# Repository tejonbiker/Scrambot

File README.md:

Scrambot
========

29/May/2014

University of Guanajuato

Division de Ingenierias Campus Irapuato Salamanca (DICIS)

Jose Federico Ramos Ortega

Scrambot is a differential mobile robot controlled via WiFi based
on a beetle robot from Steren as chassis and a Raspberry Pi as core of the controller.

This project begins with the ASME SPDC contest in 2013: "Remote Inspection Device":

https://www.asme.org/events/competitions/student-design-competition

The targets and the rules were quite simple:

    -The robot operator cannot see the stage
    -The robot need to establish (in any way) a real time video with the operator
    -The robot need to be controlled wirelessly
    -The robot need to accomplish three tasks:
      1.-Read a label with four numbers
      2.-Carry a small wood cylinder
      3.-Push a button 
          
The best balance between cost and flexibility was the Raspberry Pi with a lot of add-ons.
The result of the contest was this project (with a more little post work), this repo have the intention
to be a source of knowledge and contact that you require if you want to reconstruct/improve this project. 

Some topics/knowledge used in this robot are:

    -Remote connections
      -SSH
      -VNC
      -TCP sockets for server and client (ANSIC C and Java respectively)
      -MJPEG Server
      
    -Java Desktop GUI
      -Sockets
      -MJPEG Capture and show
      
    -PCB Design (with Eagle)
      -5V Switched Mode Power Suypply
      -Raspberry Pi GPIO and two L293 H-Bridge interface
      
    -Raspberry Pi GPIO management
      -WiringPi
      -I2C (for MPU6050 acelerometter)
      
    -Power Management 
      -Knowledge about batteries (NiCd - Lipo)
      -5V SMPS design
      -Power consumption analysis
      
    -Linux stuff
      -SSH and console commands management
      -Bash scripting
        -Automatically start services
        -Automatically install software
      -Make for compilation in ANSI C
      
    -Wireless LAN magagement
      -Detecting the Scrambot in LAN
      -Scrambot as hotspot
  
(Breathe.......) and much more.

For any misspelling/correction/comment/idea don't doubt to contact me.

tejonbiker@gmail.com

We will be happy if you like the project. 

Don't forget this is a MIT licensed project.

Have fun!!!!! :D

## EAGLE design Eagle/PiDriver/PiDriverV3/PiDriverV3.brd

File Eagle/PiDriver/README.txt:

PiDrive
This board designed to interface four motors with complete H-bridge, 
this task is accomplished with two L293 IC, some other sutff is addded,
like a PIC (MCU) to monitor the input voltage for the motors, the PIC is
not tested yet.

The board don't integrate a regulador to feed the Raspberry Pi with the
battery of the motors, this board only connect the battery for the motors.

The MPU6050 pinout works perfect.

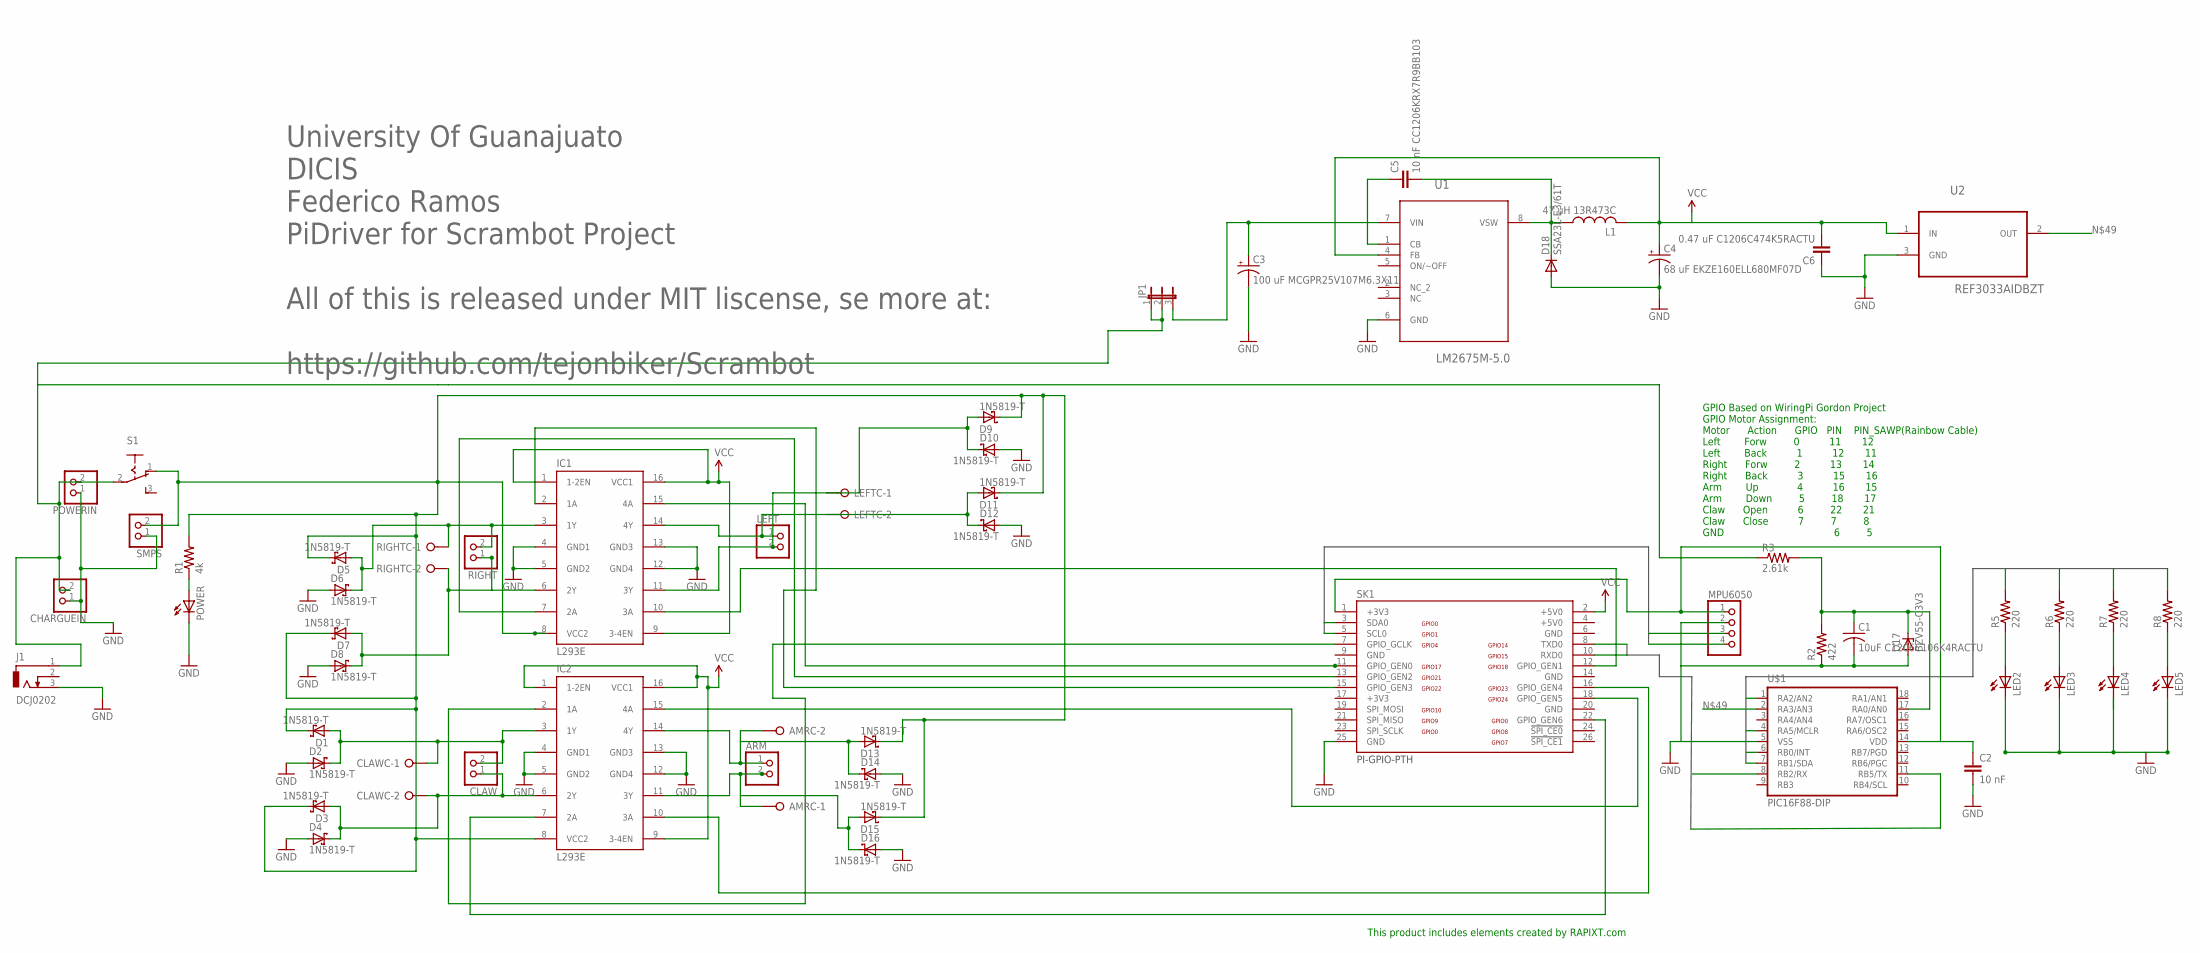
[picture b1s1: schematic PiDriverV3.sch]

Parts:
AMRC: W237-02P; W237-132
ARM: PINHD-1X2; 1X02
C1: 10uF C1206C106K4RACTU; C1206
C2: 10 nF; C1206
C3: 100 uF MCGPR25V107M6.3X11; E1,8-4
C4: 68 uF EKZE160ELL680MF07D; E1,8-4
C5: 10 nF CC1206KRX7R9BB103; C1206
C6: 0.47 uF C1206C474K5RACTU; C1206
CHARGUEIN: PINHD-1X2; 1X02
CLAW: PINHD-1X2; 1X02
CLAWC: W237-02P; W237-132
D1, D2, D3, D4, D5, D6, D7, D8, D9, D10, D11, D12, D13, D14, D15, D16: 1N5819-T; DO41-7.6
D17: BZV55-C3V3; SOD80C
D18: SSA23L-E3/61T; DO-214AC
IC1, IC2: L293E; DIL16
J1: DCJ0202
JP1: JP2E; JP2
L1: 47 uH 13R473C; 6000-XXXX-RC
LED2, LED3, LED4, LED5: LEDSMT1206; 1206
LEFT: PINHD-1X2; 1X02
LEFTC: W237-02P; W237-132
MPU6050: PINHD-1X4; 1X04
POWER: LEDSMT1206; 1206
POWERIN: PINHD-1X2; 1X02
R1: 4k; M1206
R2: 422; M1206
R3: 2.61k; M1206
R5, R6, R7, R8: 220; M1206
RIGHT: PINHD-1X2; 1X02
RIGHTC: W237-02P; W237-132
S1: 255SB
SK1: PI-GPIO-PTH; GPIO-CONNECTOR
SMPS: PINHD-1X2; 1X02
U1: LM2675M-5.0; SOIC127P620X175-8N
U2: REF3033AIDBZT; SOT95P237X112-3N
U$1: PIC16F88-DIP; DIL18

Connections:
+3V3: SK1.17 (+3V3)
+5V0: SK1.4 (+5V0)
ARMC: IC2.2 (1A), SK1.7 (GPIO_GCLK)
GND: C6.1, U2.3 (GND)
HTX: SK1.8 (TXD0), U$1.8 (RB2/RX)
unnamed: POWER.A, R1.1
unnamed: LED2.A, R5.1
unnamed: D9.A, D10.C, IC1.11 (3Y), LEFT.2, LEFTC.1
unnamed: IC2.10 (3A), SK1.16 (GPIO_GEN4)
unnamed: IC1.2 (1A), SK1.15 (GPIO_GEN3)
unnamed: IC1.7 (2A), SK1.13 (GPIO_GEN2)
unnamed: IC1.10 (3A), SK1.12 (GPIO_GEN1)
unnamed: D1.C, D3.C, D5.C, D7.C, D9.C, D11.C, D13.C, D15.C, IC1.8 (VCC2), IC2.8 (VCC2), R1.2, S1.1 (O), SMPS.2
unnamed: AMRC.2, ARM.1, D13.A, D14.C, IC2.14 (4Y)
unnamed: AMRC.1, ARM.2, D15.A, D16.C, IC2.11 (3Y)
unnamed: D11.A, D12.C, IC1.14 (4Y), LEFT.1, LEFTC.2
unnamed: R5.2, U$1.1 (RA2/AN2)
unnamed: C2.1, MPU6050.1, SK1.1 (+3V3), U$1.14 (VDD)
unnamed: IC2.15 (4A), SK1.18 (GPIO_GEN5)
unnamed: LED3.A, R6.1
unnamed: IC2.7 (2A), SK1.22 (GPIO_GEN6)
unnamed: SK1.10 (RXD0), U$1.11 (RB5/TX)
unnamed: CLAW.2, CLAWC.1, D1.A, D2.C, IC2.3 (1Y)
unnamed: D5.A, D6.C, IC1.3 (1Y), RIGHT.2, RIGHTC.1
unnamed: C5.2, D18.C, L1.1, U1.8 (VSW)
unnamed: IC1.15 (4A), SK1.11 (GPIO_GEN0)
unnamed: C3.+, JP1.3, U1.7 (VIN)
unnamed: C1.1, D17.C, R2.2, R3.2, U$1.17 (RA0/AN0)
unnamed: R6.2, U$1.4 (RA5/MCLR)
unnamed: LED4.A, R7.1
unnamed: CLAW.1, CLAWC.2, D3.A, D4.C, IC2.6 (2Y)
unnamed: D7.A, D8.C, IC1.6 (2Y), RIGHT.1, RIGHTC.2
unnamed: LED5.A, R8.1
unnamed: C5.1, U1.1 (CB)
unnamed: R7.2, U$1.6 (RB0/INT)
unnamed: C1.2, C2.2, C3.-, C4.-, CHARGUEIN.1, D2.A, D4.A, D6.A, D8.A, D10.A, D12.A, D14.A, D16.A, D17.A, D18.A, IC1.4 (GND1), IC1.5 (GND2), IC1.12 (GND4), IC1.13 (GND3), IC2.4 (GND1), IC2.5 (GND2), IC2.12 (GND4), IC2.13 (GND3), J1.3, LED2.C, LED3.C, LED4.C, LED5.C, MPU6050.2, POWER.C, POWERIN.1, R2.1, SK1.6 (GND), SK1.9 (GND), SK1.14 (GND), SK1.20 (GND), SK1.25 (GND), SMPS.1, U1.6 (GND), U$1.5 (VSS)
unnamed: R8.2, U$1.7 (RB1/SDA)
unnamed: U2.2 (OUT), U$1.2 (RA3/AN3)
unnamed: CHARGUEIN.2, J1.1, JP1.1, JP1.2, POWERIN.2, R3.1, S1.2
SCL: MPU6050.3, SK1.5 (SCL0)
SDA: MPU6050.4, SK1.3 (SDA0)
VCC: C4.+, C6.2, IC1.1 (1-2EN), IC1.9 (3-4EN), IC1.16 (VCC1), IC2.1 (1-2EN), IC2.9 (3-4EN), IC2.16 (VCC1), L1.2, SK1.2 (+5V0), U1.4 (FB), U2.1 (IN)

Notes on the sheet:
GPIO Based on WiringPi Gordon Project GPIO Motor Assignment: Motor Action GPIO PIN PIN_SAWP(Rainbow Cable) Left Forw 0 11 12 Left Back 1 12 11 Right Forw 2 13 14 Right Back 3 15 16 Arm Up 4 16 15 Arm Down 5 18 17 Claw Open 6 22 21 Claw Close 7 7 8 GND 6 5
This product includes elements created by RAPIXT.com
University Of Guanajuato DICIS Federico Ramos PiDriver for Scrambot Project All of this is released under MIT liscense, se more at: https://github.com/tejonbiker/Scrambot

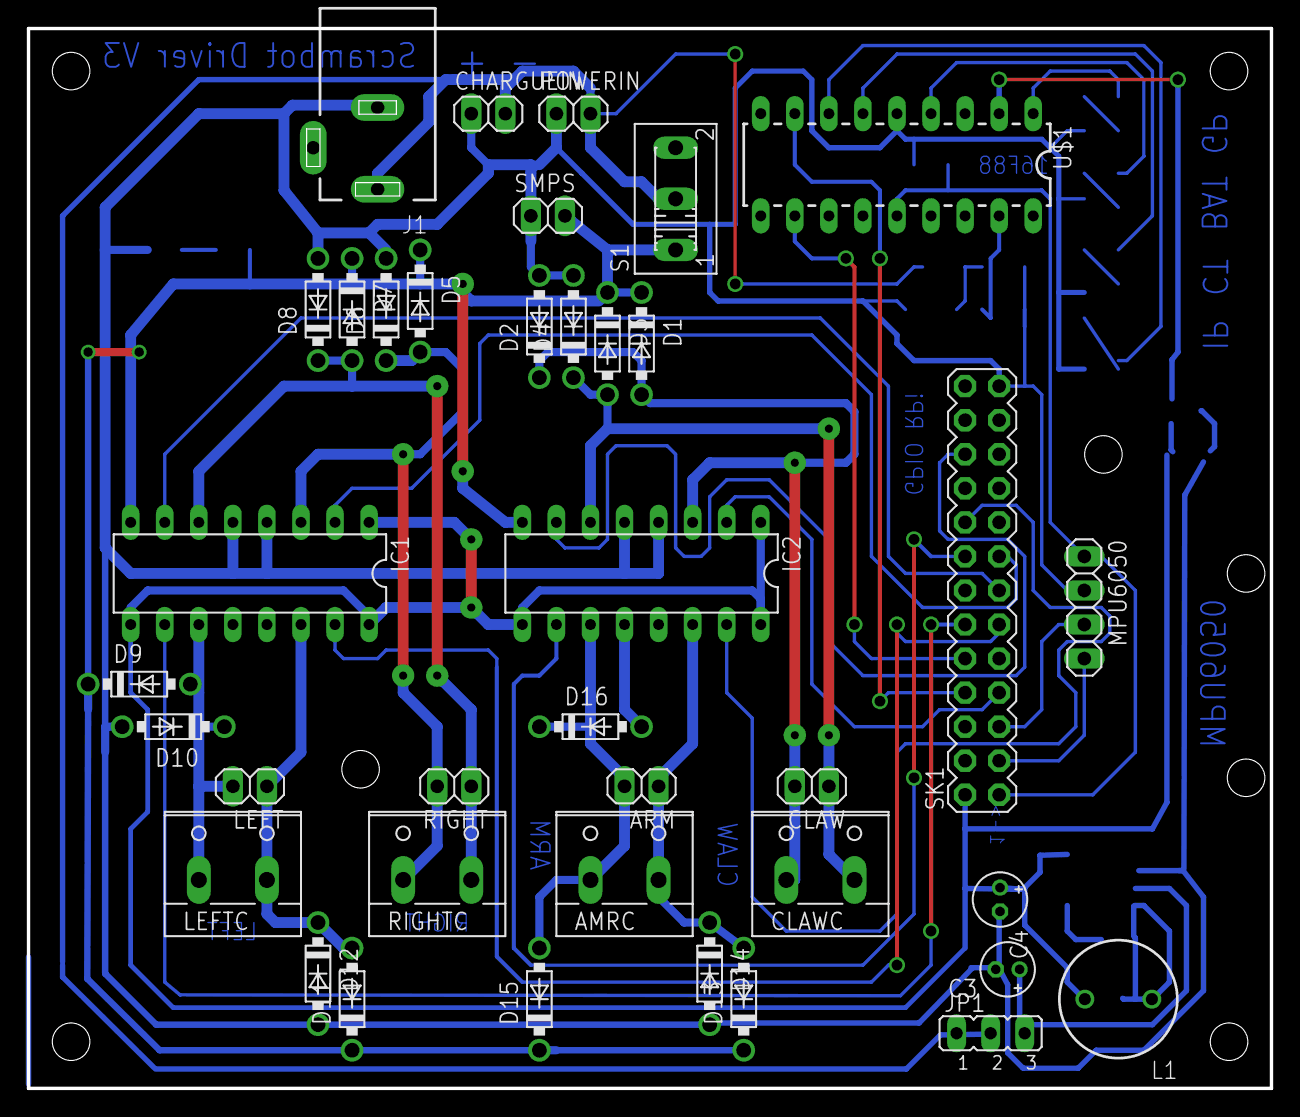
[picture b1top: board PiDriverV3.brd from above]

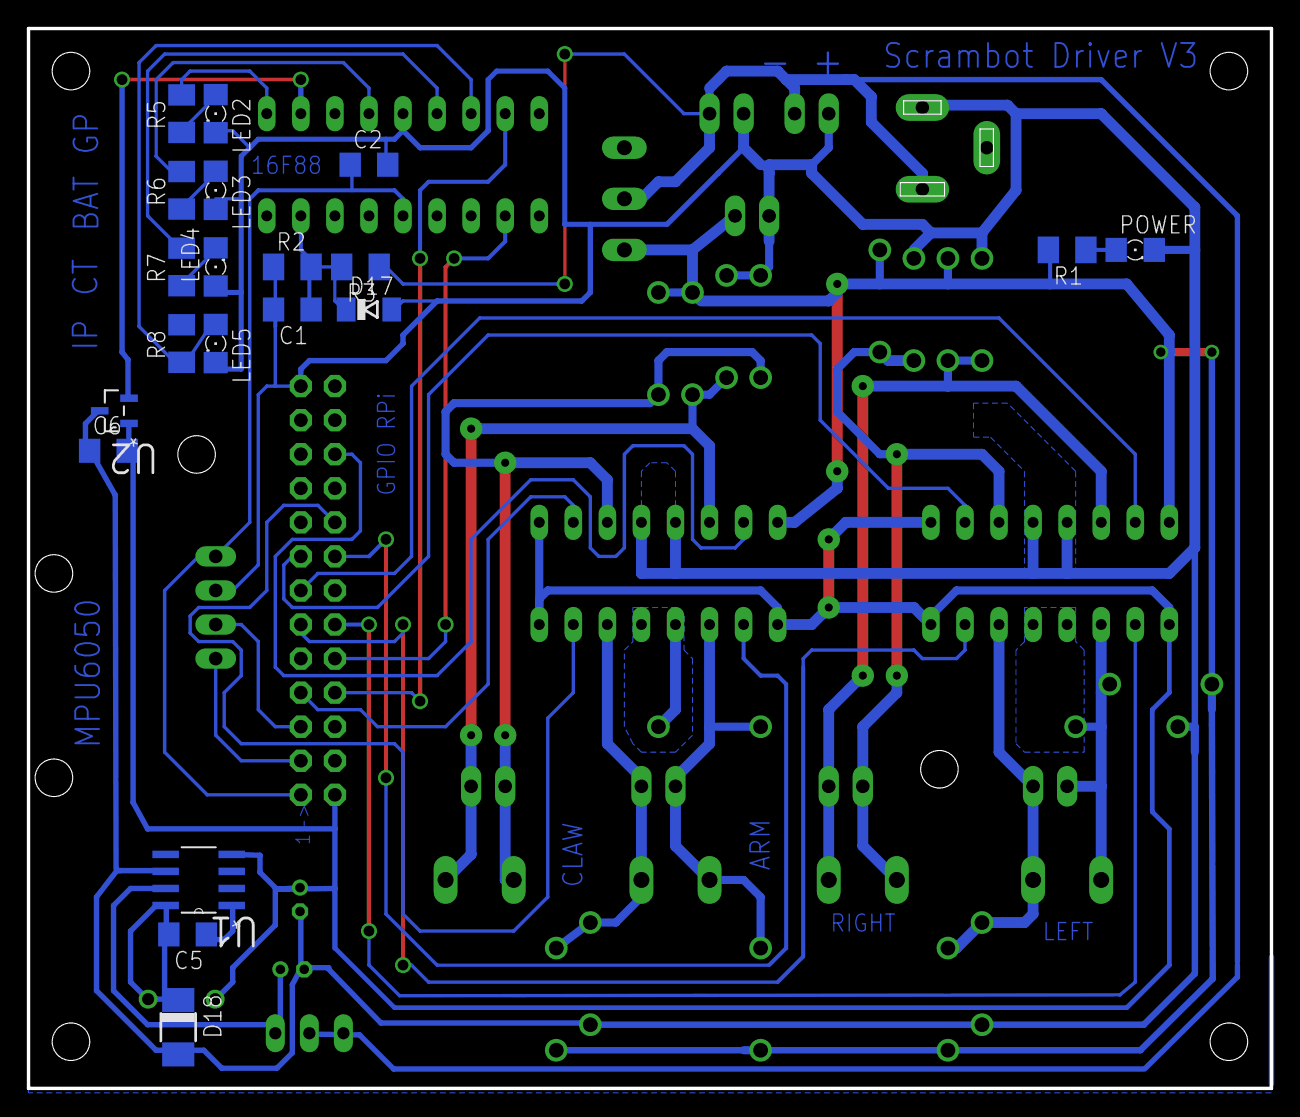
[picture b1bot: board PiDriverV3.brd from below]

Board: 2 copper layers, 92.7 x 79.0 mm, 58 parts (20 on the bottom side), 40 nets.

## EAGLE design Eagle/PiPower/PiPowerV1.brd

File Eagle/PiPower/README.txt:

PiPower
This board is designed to regulate 5V from 7V-15V battery
 voltage with an efficient  Switched Mode Power Supply, 
the board integrate an USB Female A conector to use a 
micro usb cable to power the pi, as is usual.

See more at datasheet of: LM2596

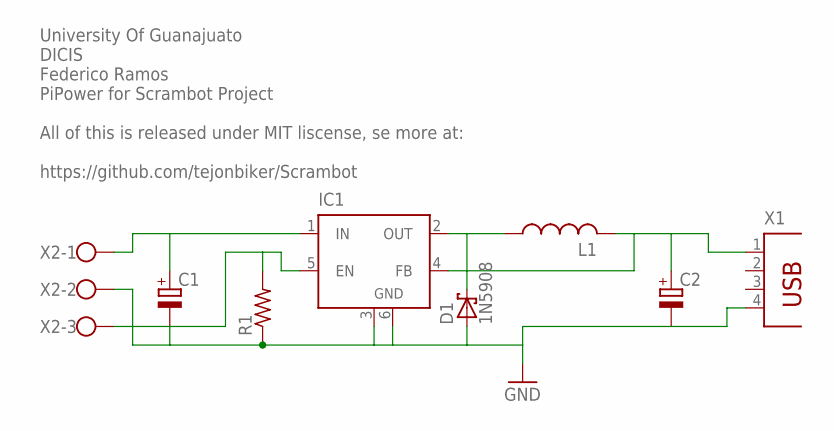
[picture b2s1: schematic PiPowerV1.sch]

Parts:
C1, C2: CPOL-EUE3.5-10; E3,5-10
D1: 1N5908; C4111-15
IC1: LM2596S; TO263-5
L1: L-US0204/5; 0204/5
R1: R-US_M1206; M1206
X1: PN87520
X2: W237-103

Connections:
unnamed: C2.+, IC1.4 (FB), L1.2, X1.1
unnamed: C1.+, IC1.1 (IN), X2.1
unnamed: IC1.5 (EN), R1.2, X2.3
unnamed: D1.C, IC1.2 (OUT), L1.1
unnamed: C1.-, C2.-, D1.A, IC1.3 (GND), IC1.6 (GND), R1.1, X1.4, X2.2

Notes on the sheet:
University Of Guanajuato DICIS Federico Ramos PiPower for Scrambot Project All of this is released under MIT liscense, se more at: https://github.com/tejonbiker/Scrambot

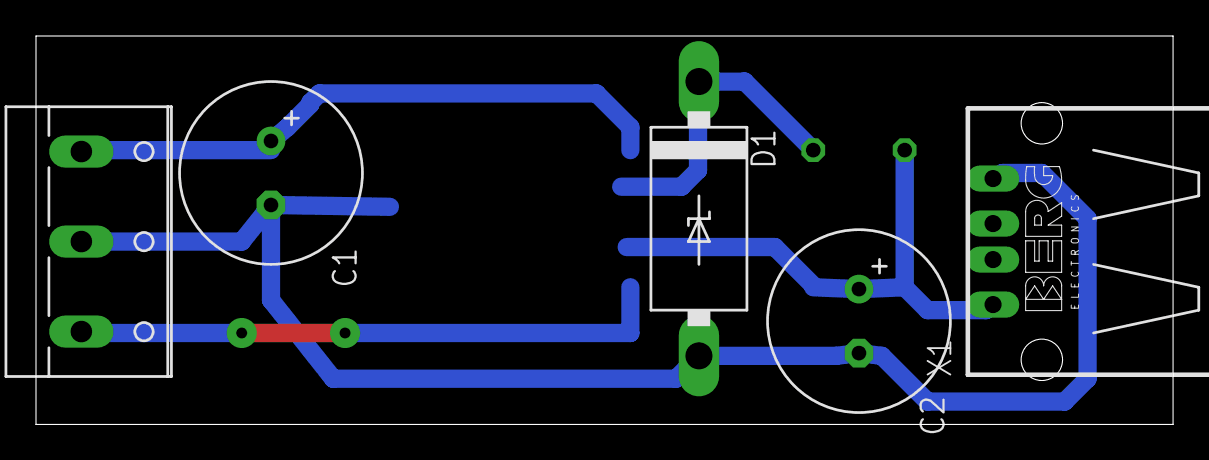
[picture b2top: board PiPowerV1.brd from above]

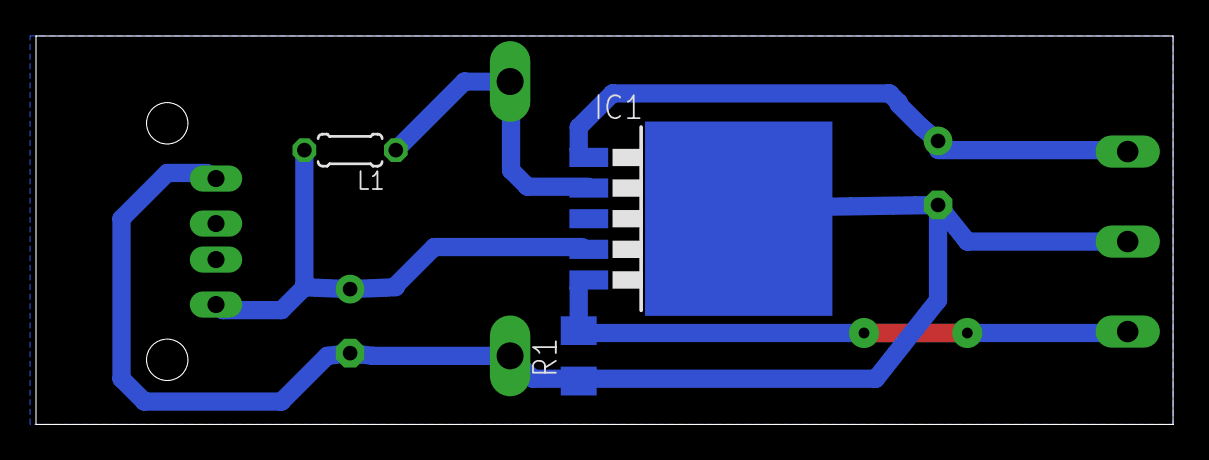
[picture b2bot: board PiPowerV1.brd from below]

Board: 2 copper layers, 63.2 x 21.6 mm, 8 parts (3 on the bottom side), 5 nets.

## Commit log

2014-05-30 Create License
2014-05-31 Inital Release
2014-05-31 Some spelling corrections in REAMDE PiDriver
2014-06-08 PiDriver V3 was added, the V2 continues for reference, the new PCB now contain clamp diodes, that allow use L293B to feed four motor up to 1 A without damage
2014-06-16 A second quote of smps for PiDrive was added
2014-06-18 An SMPS and Ref Voltage was added to PiDrive
2014-06-25 some traces were fixed, the newark bom was added

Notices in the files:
parts and their libraries:
SparkFun-DigitalIC: Licensing: CC v3.0 Share-Alike You are welcome to use this library for commercial purposes.
